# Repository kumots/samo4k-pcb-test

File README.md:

# Pagsamo - Noun in Tagalog, something one yearns for, or pleas for.
I have no idea how this is related to the project, but it just sounds cool.

Anyways, this is just a simple 2x2 keypad that you can order and assemble yourself to practice your skills in soldering and electronic work overall.
You can download the ZIP file containing all the gerber files and upload it to JLCPCB or any other platform that offers PCB printing services. You can also
refer to the attatched schematics and PCB KiCad files for further details.

This keypad is powered with a Mini-USB slot for simplicity, and also does not come with hotswap sockets, unfortunately(I don't know how to add them lmao).

Parts you will need to order:

**x3 0.1uF Ceramic Capacitator, 0805 Package**

**x1 10uF Ceramic Capacitator, 0805 Package**

**x1 1uF Ceramic Capacitator, 0805 Package**

**x2 22pF Ceramic Capacitator, 0805 Package**

**x4 Generic Diode, SOD-123 Package**

**x1 500mA Hold 1A Trip Polyfuse, 1206 Package**

**x2 10k Resistor, 0805 Package**

**x2 22 Resistor, 0805 Package**

**x1 Low Profile Tactile Switch, 5.2x5.2mm Package**

**x1 ATMEGA32U4 Microcontroller, 44TQFP 10x10mm Package**

**x1 Molex Mini-B USB C Receptacle, Molex-0548190589 Package**

**x1 16MHz Crystal, 3.2x2.5mm 4 pad Package**

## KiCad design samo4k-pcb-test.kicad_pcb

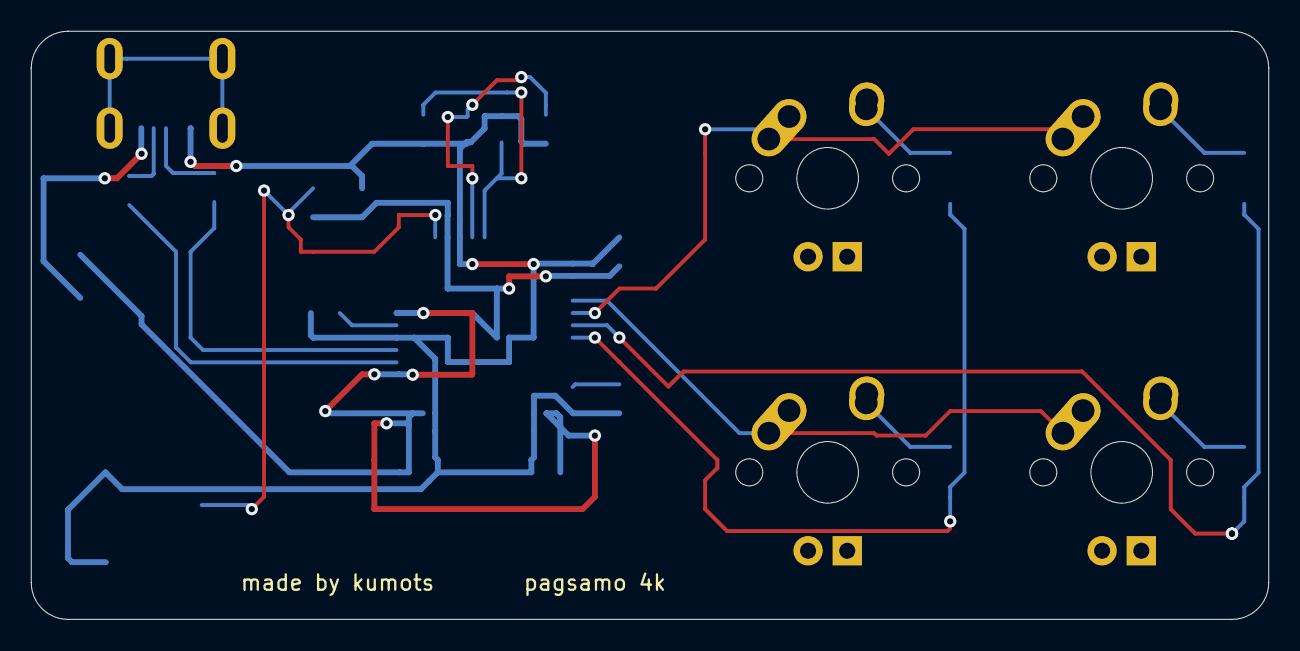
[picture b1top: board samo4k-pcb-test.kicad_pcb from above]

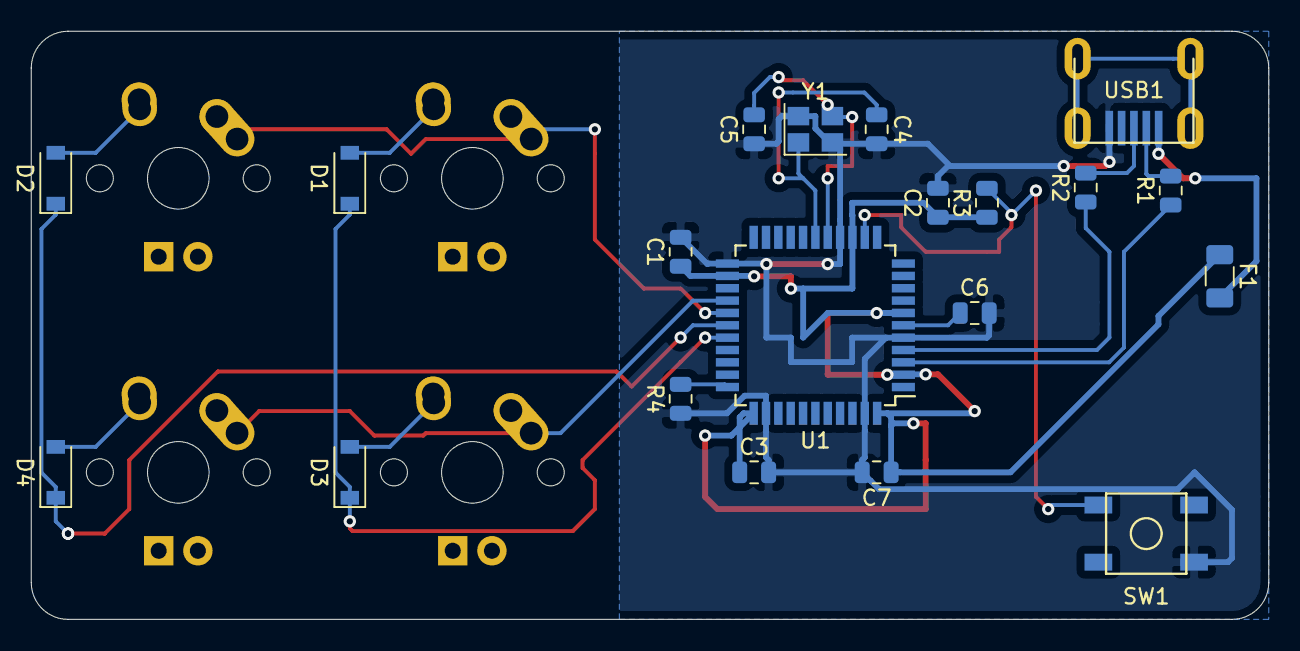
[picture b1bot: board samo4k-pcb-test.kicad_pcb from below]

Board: 2 copper layers, 80.2 x 38.1 mm, 24 parts (20 on the bottom side), 20 nets.

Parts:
C1, C2, C3: 0.1uF; C_0805_2012Metric
C4, C5: 22pF; C_0805_2012Metric
C6: 1uF; C_0805_2012Metric
C7: 10uF; C_0805_2012Metric
D1, D2, D3, D4: SOD-123; D_SOD-123
F1: 500mA; Fuse_1206_3216Metric
MX1, MX2, MX3, MX4: MX-NoLED; MX-1U
R1, R2: 22; R_0805_2012Metric
R3, R4: 10k; R_0805_2012Metric
SW1: SW_Push; SKQG-1155865
U1: ATmega32U4-AU; TQFP-44_10x10mm_P0.8mm
USB1: Molex-0548190589
Y1: 16MHz; Crystal_SMD_3225-4Pin_3.2x2.5mm

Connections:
+5V: C1.1, C2.1, C3.1, C7.1, F1.1, R3.1, U1.2, U1.7, U1.14, U1.24, U1.34, U1.44
COL0: MX1.1, MX2.1, U1.27
COL1: MX3.1, MX4.1, U1.26
D+: R2.2, USB1.3
D-: R1.2, USB1.4
GND: C1.2, C2.2, C3.2, C4.2, C5.1, C6.2, C7.2, R4.1, SW1.1, U1.5, U1.15, U1.23, U1.35, U1.43, USB1.1, Y1.2, Y1.4
unnamed: C4.1, U1.17, Y1.1
unnamed: C5.2, U1.16, Y1.3
unnamed: C6.1, U1.6
unnamed: D1.2, MX1.2
unnamed: D2.2, MX2.2
unnamed: D3.2, MX3.2
unnamed: D4.2, MX4.2
unnamed: R1.1, U1.3
unnamed: R2.1, U1.4
unnamed: R3.2, SW1.2, U1.13
unnamed: R4.2, U1.33
ROW0: D1.1, D3.1, U1.29
ROW1: D2.1, D4.1, U1.28
VCC: F1.2, USB1.5

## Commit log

2024-07-21 basic files
2024-07-21 submodules
2024-07-21 submods implemented
2024-07-22 schematics
2024-07-22 silks
2024-07-22 gerbers and final changes for now
2024-07-24 readme created
